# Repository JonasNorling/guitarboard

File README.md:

The Cortex Guitar Board
=======================

This is a Cortex-M4 DSP board for development of audio DSP
applications such as Guitar effects.

This repository contains the hardware design as KiCAD files and sample
software that implements some naive guitar effects. For info about the
software and how to load it, look at [fw/README.md](fw/README.md). For
more on the hardware, keep on reading below and also look in
[hw/README.md](hw/README.md).

The board is based on a STM32F405RG microcontroller (192KiB RAM,
Cortex-M4 with DSP and floating point instructions) and a WM8731 audio
codec.

About the hardware
------------------

### Audio chain

The stereo audio input is pre-amplified in an opamp before the signal
reaches the ADC. This step is required to get a high input impedance
suitable for connecting to an electric guitar or other passive
systems. A WM8731 audio codec is used to digitize the audio signal and
feed it over an I2S bus to the STM32 MCU, and to convert the resulting
signal back into the analog domain. The codec chip includes an
amplifier so the board is capable of driving low-impedance loads such
as headphones.

Note that this isn't quite a HiFi system, though it should be good
enough for casual use. For example, there is some theoretical
crosstalk between the L/R channels on the input side (although you
won't hear it), the codec isn't particularly fancy and expensive, and
the USB power supply isn't very well filtered. If the audio input is
clipping because whatever you're feeding in is too high level (more
than, say, 1V RMS), attenuate it a bit with a resistor divider first.

### Powering the board

The board is designed to be deployed in an effects pedal or box or in
the wiring compartment in an electric guitar. To avoid ground loops it
should run from battery power or an isolated power supply (not mains
earth referenced).

The acceptable input voltage is around 4 to 9 V and the current draw
lands at about 80mA (168MHz, 25% CPU awake) — that should give you
about 24 hours runtime on 4 AA cells.

There is also a micro-USB connector on the board that can be used to
provide power. Note that the USB bus power is connected to the power
input terminal, so avoid connecting another power supply (such as a
battery) at the same time as USB. The USB power from a computer can be
quite noisy, so it may be a bad idea to use it from an audio quality
point of view. Also, connecting the audio output to the same computer
or another grounded system will create funny ground effects that add
additional noise components. Note that there is no inrush current
limit on the USB power line, which is in conflict with requirements in
the USB standard. This might make some USB hosts turn off the port,
although most seem to be just fine with it.

### I/O options

* Micro-USB connector
* 2 LEDs (green and amber, 3mm throughhole) or 2.54mm header
* 2.54mm header with power, 6 analog capable GPIO pins, UART RX/TX and
  1 digital pin
* 3.5mm stereo audio output jack (headphone amplified)
* 3.5mm stereo audio input jack (high impedance)
* optional stereo line-out header
* ARM SWD debug/programming connector, 10-pin 1.27mm pitch

#### MIDI

There are no MIDI ports on board, but the exposed UART pins could be
used to hook up MIDI connectors with a few external parts.

Other resources
---------------

* [Elemental Instruments](http://www.elemental.se)
* [Project on Hackaday.io](https://hackaday.io/project/7936-cortex-guitar-board)

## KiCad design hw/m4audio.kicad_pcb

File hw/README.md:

This directory contains the hardware design in KiCAD format.

Board changelog and errata
--------------------------

### Errata for board revision C

- Line out is missing footprints for some of the resistors recommended
  in the datasheet. It has not been tested.
- Missing a discharge path for the audio input, as recommended in the
  datasheet. I don't think it's necessary in this application.
- There is too much capacitance on the board to comply with the USB
  standard, and inrush current is not limited.
- Silkscreen showing orientation of opamp and codec are unclear on
  finished board.
- Some silkscreen text is too small.
- Drills on TPs are too large for their pads for some processes.
- Solder bridge potential on opamp pins 1 and 2 (doesn't matter).

### Changes in board revision C

- The ground plane has been redesigned; the audio and digital parts
  are now joined in only one point. This was done with the hope of
  minimising audible interference from the MCU.
- Hole and pad sizes for test points have been adjusted, because ITEAD
  Studio had trouble manufacturing rev.B boards without meddling with
  holes and pads.
- Now using two smaller voltage regulators to further separate audio
  and MCU.
- C28, the bulk capacitor before the voltage regulator has been
  removed.
- The diode ORing power from USB or the other connector has been
  removed. It was felt that the voltage drop was slightly troublesome
  and it was better to allow a slightly lower battery voltage instead.
- Footprints for SMD LEDs removed; use 2.54mm header or leaded LEDs.
- Moved stuff around a bit ("optimised component placement").
- RST header.

### Errata for board revision B

- The bulk capacitor upstream of the voltage regulator, C28, should
  not be mounted. It has been discovered that it couples noise from
  the MCU into the ground plane close to the codec. Putting a
  capacitor there makes the audible noise more noticable.
- Putting a resistor (roughly 2-30 ohms) or an inductor in the analog
  power supply path improves audible noise. This can be achieved by
  scraping open the net tie W2 on the backside of the board and
  mounting a 0805 on 1206 resistor there.
- The pin marked PA8 on the silkscreen is in fact not PA8.

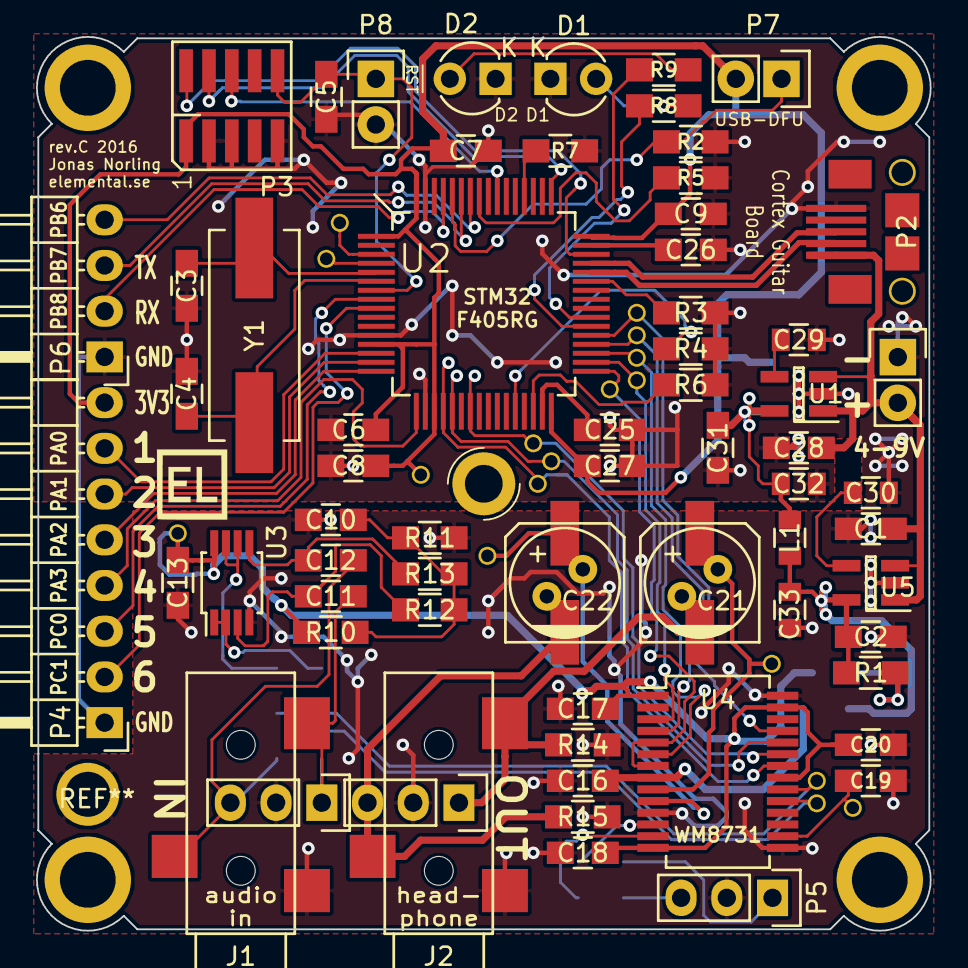
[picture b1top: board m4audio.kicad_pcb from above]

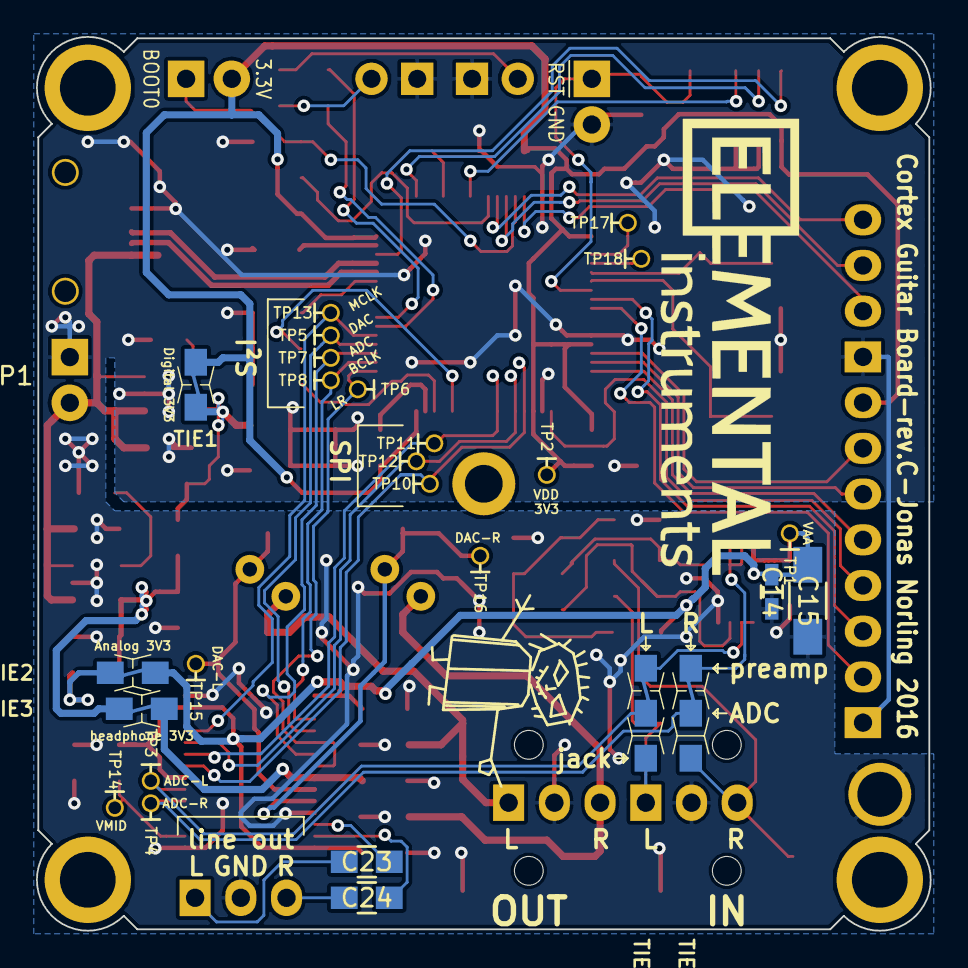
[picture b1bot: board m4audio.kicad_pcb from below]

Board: 2 copper layers, 49.7 x 49.7 mm, 91 parts (26 on the bottom side), 67 nets.

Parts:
C1, C28: 10u16V; C_0805_HandSoldering
C2, C10, C13, C16, C17, C18, C19, C20, C31: 10u; C_0805_HandSoldering
C3, C4: 27p; C_0805_HandSoldering
C5, C7, C8, C9, C11, C12, C27: 100n; C_0805_HandSoldering
C6: 1u; C_0805_HandSoldering
C14: DNP; C_0603_HandSoldering
C15: DNP; C_1206_HandSoldering
C21, C22: 220u; c_elec_6.3x7.7
C23, C24: DNP; C_0805_HandSoldering
C25, C26: 2.2u; C_0805_HandSoldering
C29, C30, C32, C33: DNP; C_0805
D1: green; LED-3MM
D2: orange; LED-3MM
J1, J2: JACK_TRS; 35RASMT2BHNTRX
J11, J21: CONN_01X03; Pin_Header_Straight_1x03
L1: DNP; C_0805
P1, P7, P8: CONN_01X02; Pin_Header_Straight_1x02
P2: USB_OTG; USB_Micro_FCI
P3: CONN_02X05; Pin_Header_SMT_1.27_2x5
P4: CONN_01X08; Pin_Header_Angled_1x08
P5: CONN_01X03; Pin_Header_Straight_1x03
P6: CONN_01X04; Pin_Header_Angled_1x04
R1: 10; R_0805_HandSoldering
R2, R3, R4, R5, R6, R7, R10, R11, R14, R15: 100k; R_0805_HandSoldering
R8, R9: 470; R_0805_HandSoldering
R12, R13: 560k; R_0805_HandSoldering
TIE1: V_D; net_tie_0805
TIE2: V_A; net_tie_0805
TIE3: V_HP; net_tie_0805
TIE4, TIE5: CONN_01X03; net_tie_3_0805
TP1, TP2, TP3, TP4, TP5, TP6, TP7, TP8, TP10, TP11, TP12, TP13, TP14, TP15, TP16, TP17, TP18: TST; TP_0.7mm
U1, U5: AP2210K-3.3; SOT-23-5_Handsoldering
U2: STM32F405RG; QFP50P1200X1200-64
U3: MCP6002; MSOP-8_3x3mm_Pitch0.65mm
U4: WM8731; SSOP-28_5.3x10.2mm_Pitch0.65mm
Y1: 8MHz; Crystal_HC49-SD_SMD

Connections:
/APWR: C2.1, C33.1, L1.1, R1.1, TIE3.2, U5.5
/BOOT0: P7.1, R2.2, U2.60
/BOOT1: R4.2, U2.28
/BYP1: C29.1, U1.4
/BYP2: C30.1, U5.4
/DPWR: C31.1, C32.2, L1.2, TIE1.2, U1.5
/LED1: R8.2, U2.38
/LED2: R9.2, U2.39
/MISC1: P4.7, U2.14
/MISC2: P4.6, U2.15
/MISC3: P4.5, U2.16
/MISC4: P4.4, U2.17
/MISC5: P4.3, U2.8
/MISC6: P4.2, U2.9
/NRST: C5.1, P3.10, P8.1, U2.7
/OSCIN: C3.1, U2.5, Y1.1
/OSCOUT: C4.1, U2.6, Y1.2
/PB6: P6.4, U2.58
/PB7: P6.3, U2.59
/PB8: P6.2, U2.61
/PWR_5V: C1.1, C28.1, P1.2, P2.1, U1.1, U1.3, U5.1, U5.3
/SWCLK: P3.4, U2.49
/SWDIO: P3.2, U2.46
/SWO: P3.6, U2.55
/USB_DM: P2.2, U2.44
/USB_DP: P2.3, U2.45
/VCAP1: C25.1, U2.31
/VCAP2: C26.1, U2.47
/audio/ADCDAT: TP7.1, U2.35, U4.6
/audio/ADCL: TIE4.2, TP3.1, U4.20
/audio/ADCLR: TP6.1, U2.33, U4.5, U4.7
/audio/ADCR: TIE5.2, TP4.1, U4.19
/audio/AIN_L: C11.2, J1.2, J11.1, TIE4.3
/audio/AIN_R: C12.2, J1.3, J11.3, TIE5.3
/audio/AOUT_L: C21.2, J2.2, J21.1, R14.1
/audio/AOUT_R: C22.2, J2.3, J21.3, R15.1
/audio/BCLK: TP8.1, U2.34, U4.3
/audio/CS: TP10.1, U2.20, U4.22
/audio/DACDAT: TP5.1, U2.36, U4.4
/audio/DACL: C21.1, TP15.1, U4.9
/audio/DACR: C22.1, TP16.1, U4.10
/audio/LINEL: C23.1, U4.12
/audio/LINER: C24.1, U4.13
/audio/MCLK: TP13.1, U2.37, U4.25
/audio/MOSI: TP11.1, U2.23, U4.23
/audio/OPINL: C11.1, R12.2, U3.3
/audio/OPINR: C12.1, R13.1, U3.5
/audio/OPOUTL: TIE4.1, U3.1, U3.2
/audio/OPOUTR: TIE5.1, U3.6, U3.7
/audio/SCLK: TP12.1, U2.21, U4.24
/audio/VMID: C19.2, TP14.1, U4.16
/audio/bias: C10.2, R10.1, R11.2, R12.1, R13.2
GND: C1.2, C2.2, C3.2, C4.2, C5.2, C6.2, C7.2, C8.2, C9.2, C10.1, C13.1, C14.1, C15.1, C16.1, C17.1, C18.1, C19.1, C20.1, C25.2, C26.2, C27.2, C28.2, C29.2, C30.2, C31.2, C32.1, C33.2, D1.1, D2.1, J1.1, J2.1, J11.2, J21.2, P1.1, P2.5, P3.3, P3.5, P3.9, P4.1, P5.2, P6.1, P8.2, R2.1, R3.2, R4.1, R5.1, R6.1, R7.1, R11.1, R14.2, R15.2, U1.2, U2.12, U2.18, U2.63, U3.4, U4.11, U4.15, U4.28, U5.2
HPVDD: C16.2, TIE3.1, U4.8
unnamed: C23.2, P5.1
unnamed: C24.2, P5.3
unnamed: D1.2, R8.1
unnamed: D2.2, R9.1
unnamed: R1.2, TIE2.2
unnamed: R3.1, U2.43
unnamed: R5.2, U2.57
unnamed: R6.2, U2.30
unnamed: R7.2, U2.52
unnamed: TP17.1, U2.3
unnamed: TP18.1, U2.4
VAA: C13.2, C14.2, C15.2, C17.2, C18.2, C20.2, R10.2, TIE2.1, TP1.1, U3.8, U4.1, U4.14, U4.21, U4.27
VDD: C6.1, C7.1, C8.1, C9.1, C27.1, P3.1, P4.8, P7.2, TIE1.1, TP2.1, U2.1, U2.13, U2.19, U2.32, U2.48, U2.64

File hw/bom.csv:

Reference,Value,Footprint,Mouser,Notes
C1,10u16V,Capacitors_SMD:C_0805_HandSoldering,81-GRM21BC81C106KE5L,"This Murata is X6S (5.9u biased at 5V)"
C10,10u,Capacitors_SMD:C_0805_HandSoldering,81-GRM21R60J106KE19L,"This Murata is X5R 6.3V (7.5u biased at 3.3V)"
C11,100n,Capacitors_SMD:C_0805_HandSoldering,581-08055C104KAT4A,"This AVX is X7R 50V"
C12,100n,Capacitors_SMD:C_0805_HandSoldering,,
C13,10u,Capacitors_SMD:C_0805_HandSoldering,,
C14,DNP,Capacitors_SMD:C_0603_HandSoldering,,
C15,DNP,Capacitors_SMD:C_1206_HandSoldering,,
C16,10u,Capacitors_SMD:C_0805_HandSoldering,,
C17,10u,Capacitors_SMD:C_0805_HandSoldering,,
C18,10u,Capacitors_SMD:C_0805_HandSoldering,,
C19,10u,Capacitors_SMD:C_0805_HandSoldering,,
C2,10u,Capacitors_SMD:C_0805_HandSoldering,,
C20,10u,Capacitors_SMD:C_0805_HandSoldering,,
C21,220u,Jonas_caps:c_elec_6.3x7.7,647-UUR1C221MCL6GS,
C22,220u,Jonas_caps:c_elec_6.3x7.7,,
C23,DNP,Capacitors_SMD:C_0805_HandSoldering,,
C24,DNP,Capacitors_SMD:C_0805_HandSoldering,,
C25,2.2u,Capacitors_SMD:C_0805_HandSoldering,81-GRM21BR71A225KA01,"This Murata is X7R 10V"
C26,2.2u,Capacitors_SMD:C_0805_HandSoldering,,
C27,100n,Capacitors_SMD:C_0805_HandSoldering,,
C28,10u16V,Capacitors_SMD:C_0805_HandSoldering,,
C29,DNP,Capacitors_SMD:C_0805,,
C3,27p,Capacitors_SMD:C_0805_HandSoldering,80-C0805C270K5G,
C30,DNP,Capacitors_SMD:C_0805,,
C31,10u,Capacitors_SMD:C_0805_HandSoldering,,
C32,DNP,Capacitors_SMD:C_0805,,
C33,DNP,Capacitors_SMD:C_0805,,
C4,27p,Capacitors_SMD:C_0805_HandSoldering,,
C5,100n,Capacitors_SMD:C_0805_HandSoldering,,
C6,1u,Capacitors_SMD:C_0805_HandSoldering,,
C7,100n,Capacitors_SMD:C_0805_HandSoldering,,
C8,100n,Capacitors_SMD:C_0805_HandSoldering,,
C9,100n,Capacitors_SMD:C_0805_HandSoldering,,
D1,green,Footprints:LED-3MM,,
D2,orange,Footprints:LED-3MM,,
J1,JACK_TRS,Jonas_Connectors:35RASMT2BHNTRX,502-35RASMT2BHNTRX,
J11,CONN_01X03,Pin_Headers:Pin_Header_Straight_1x03,,
J2,JACK_TRS,Jonas_Connectors:35RASMT2BHNTRX,,
J21,CONN_01X03,Pin_Headers:Pin_Header_Straight_1x03,,
L1,DNP,Capacitors_SMD:C_0805,,
P1,CONN_01X02,Pin_Headers:Pin_Header_Straight_1x02,,
P2,USB_OTG,Jonas_Connectors:USB_Micro_FCI,649-10118193-0001LF,
P3,CONN_02X05,Jonas_Connectors:Pin_Header_SMT_1.27_2x5,649-202112100010C4LF,
P4,CONN_01X08,Pin_Headers:Pin_Header_Angled_1x08,,
P5,CONN_01X03,Pin_Headers:Pin_Header_Straight_1x03,,
P6,CONN_01X04,Pin_Headers:Pin_Header_Angled_1x04,,
P7,CONN_01X02,Pin_Headers:Pin_Header_Straight_1x02,,
P8,CONN_01X02,Pin_Headers:Pin_Header_Straight_1x02,,
R1,10,Resistors_SMD:R_0805_HandSoldering,,
R10,100k,Resistors_SMD:R_0805_HandSoldering,754-RR1220P-104D,
R11,100k,Resistors_SMD:R_0805_HandSoldering,,
R12,560k,Resistors_SMD:R_0805_HandSoldering,"754-RR1220P-564D ",
R13,560k,Resistors_SMD:R_0805_HandSoldering,,
R14,100k,Resistors_SMD:R_0805_HandSoldering,,
R15,100k,Resistors_SMD:R_0805_HandSoldering,,
R2,100k,Resistors_SMD:R_0805_HandSoldering,,
R3,100k,Resistors_SMD:R_0805_HandSoldering,,
R4,100k,Resistors_SMD:R_0805_HandSoldering,,
R5,100k,Resistors_SMD:R_0805_HandSoldering,,
R6,100k,Resistors_SMD:R_0805_HandSoldering,,
R7,100k,Resistors_SMD:R_0805_HandSoldering,,
R8,470,Resistors_SMD:R_0805_HandSoldering,,
R9,470,Resistors_SMD:R_0805_HandSoldering,,
U1,AP2210K-3.3,Footprints:SOT-23-5_Handsoldering,621-AP2210K-3.3TRG1,"alt: NJM2866F33-TE1, alt: LP2985"
U2,STM32F405RG,Jonas_QFP:QFP50P1200X1200-64,511-STM32F405RGT6,
U3,MCP6002,Housings_SSOP:MSOP-8_3x3mm_Pitch0.65mm,,"MCP6002T-I/MS, LMR358FVM-GTR, TLV272CM8-13"
U4,WM8731,Housings_SSOP:SSOP-28_5.3x10.2mm_Pitch0.65mm,238-WM8731SEDS/V,
U5,AP2210K-3.3,Footprints:SOT-23-5_Handsoldering,,
Y1,Crystal,Crystals:Crystal_HC49-SD_SMD,815-ABLS-8-B2,

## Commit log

2015-08-03 Initial
2015-08-04 PCB updates
2015-08-04 Work...
2015-08-05 Change to electrolytic cap, routing
2015-08-05 Routing...
2015-08-08 Add WM8731 audio codec
2015-08-08 Add a gnome
2015-08-08 Tuning PCB
2015-08-09 Use only one supply net name, add VCAP on STM32, alternative LED footprints
2015-08-09 Tune PCB design, add protection diode
2015-08-09 Add I2S test pads
2015-08-09 Standardise on 100k for random stuff
2015-08-09 Tune values, add BOM
2015-08-09 Adding Gerbers used for OSH Park order
2015-08-11 Basic Eclipse project for the firmware
2015-08-13 Tune build flags and add some code to theoretically make it run
2015-08-13 Eclipse project updates
2015-08-15 Init git submodules in makefile
2015-08-15 Use C11
2015-08-15 WIP: Enable more peripherals
2015-08-15 Build rules for host
2015-08-15 Run in Jack on host
2015-08-29 Board bringup
    - The Codec can output audio though the headphone connectors
2015-08-29 Sinewave example
    There is still plenty of time available per frame.
2015-08-29 DMA data from ADC
2015-08-29 LED abstraction
2015-08-29 Simple delay line example
2015-08-31 Read analog pins
2015-09-06 Start sketching on an fxbox program, misc work
2015-09-06 Add biquad filter core, Wahwah effect, utils for buffer conversion
2015-09-17 Delay effect, the parameterization is still quite weird
2015-09-17 Simple effect selector, idle callback
2015-09-17 Vibrato effect
    knob0 - depth
    knob1 - speed
    knob2 - tubelike distortion
    knob3 - stereo effect (phase difference L/R)
2015-09-22 Effect parameters, scaling
2015-09-24 Recalculate delay each sample, yields smoother changes
2015-09-24 Pitch pedal effect, not very enjoyable
2015-09-26 DFU (USB) programming make rules
2015-09-26 Board update and ripup: split power supply, 49.5mm size
2015-09-26 Remove USB resistor, the STM32 has one built in
2015-09-26 Make TPs a bit larger
2015-09-30 Board...
2015-10-01 Put a 2mm hole in the middle, adjust routing
2015-10-03 Small fixes to routing, silkscreen
2015-10-03 Tidy up routing, add OSHW logo
2015-10-03 Board revision B finished
2015-10-04 Add README file and licenses
2015-10-05 Add missing STM32 library
2015-10-05 Update schematic metadata
2015-10-05 Use Gerber filenames for ITEAD
2015-10-11 Update libopencm3
2015-10-11 Add README.md in the firmware directory
2015-10-25 Add USB connectivity, opening a CDC ACM port for logging
    It's not rock solid, but it seems to enumerate almost every time now.
2015-10-31 Refactor how effects are called
    Using float buffers, move gain/distortion to the common code path.
2015-11-15 Add an experimental "octaver" feedback feature to the delay
    Play back the delay line at double rate and feed it back, creating a
    frequency doubler effect. It sounds interresting, but pretty rough.
2015-11-16 Refactor DSP effects a bit more
2015-11-17 Split up makefiles
    The makefile is divided into platform specific parts.
2015-11-21 Embedded guitar board software
    Support a board embedded in a guitar, with four knobs and a
    three-position switch connected.
    Select the effect to use based on the switch: delay - clean - vibrato.
    - Add functions for setting codec volume
    - Add knob configuration (ADC or GPIO input with pullup)
2016-07-06 Update DFU commands, USB descriptor
2016-07-06 Program for an effects box with switches
2016-07-06 Re-save board with KiCad 4.0, fix small compatibility error
2016-07-06 Turn off reference and value on silkscreen in Gerber
2016-07-08 Adjust testpoint drill and annular, for ITEAD production
2016-07-08 Add RST test point
2016-07-09 Use dual SMT/through hole footprint for caps
2016-07-09 Silkscreen text fixes
2016-07-16 Add delay to fxbox2
2016-07-16 Change LED footprints and resistors, RST header, hole in GND pad
2016-07-24 Redo power supply, split ground plane
    Change to using two SOT-23-5 voltage regulators, one for analog and
    one for digital. Split the ground plane so that digital and analog
    meat at only one point, hoping to improve ground coupled noise
    performance.
    Update silkscreen texts to "rev.C".
    Move silkscreen texts.
2016-07-24 Net tie to bypass the pre-amp
2016-07-25 Tiny silk fixes
2016-07-26 Tiny routing fixes
2016-08-05 Adjust USB interrupts, reset, re-enable USB log
    Logging over USB has been pretty flaky, device enumeration often not
    working. There have been hints that the USB interrupt isn't serviced
    quickly enough, but also about the interrupt not happening at all.
    Trying to fix this by properly setting up interrupt priorities so that
    USB can preempt everything else and get its shit done quickly. Trying
    to reset the USB peripheral more thoroughly, and trying to not block
2016-08-06 Update BOM
2016-08-11 Fix build warnings/errors on older compiler
2016-08-12 Add README about the board layout, update root README
2016-08-12 Add schematic PDF
2016-08-13 Add gerbers for rev.C, move them
2016-08-13 Move value texts, make PDF with assembly drawing
2016-08-13 Convert BOM to CSV format
    So that people without Gnumeric can read it.
2016-08-14 Change LED pins, for rev.C board
    Also make the feedthrough program blink in a more enticing manner.
2016-08-14 Include Kiss FFT
    This is the Kiss FFT library (sourceforge.net/projects/kissfft). After
    testing libfftw3 and getting annoyed at how hard it is to use and
    build and how enormous it is (600KiB!!!), I found Kiss FFT. It is
    slightly faster on Cortex-M3, and very easy to use and build. BSD
    license.
2016-08-14 Noise floor test
2016-08-14 Test crosstalk between channels
2016-08-14 Run THD test on both channels simultaneously
2016-08-14 Measure THD using FFT
2016-08-14 Run multiple THD tests
2016-08-14 Use a precomputed window for the FFT
2016-08-21 Remove a leftover sqrt that broke THD numbers
2016-08-21 Update BOM/schematic with component choices
    Using MCP6002 opamp, 10 ohms impedance on analog supply, not
    populating voltage regulator bypass cap by default.
2016-08-24 Read the right audio-in DMA buffer at the right time
    It seems like we've been reading the wrong buffer, but getting away
    with it because we generally read the samples right away to convert
    them to floats.
    Now using the "input" DMA interrupt, which comes 20us later, because
    the last sample hasn't been DMA's in yet when the "output" interrupt
    comes.
2016-08-24 Disable automatic high-pass in ADC, doing it in software
    This fixes some noise issues with the WM8731 codec, for some weird
    reasons. The ADC really doesn't like it when it's quiet, when it's
    sitting just around digital 0, and it seems to start to invent
    noise. Disabling removing of the DC bias (an offset which seems to be
    internal to the codec anyway) makes the signal much cleaner when the
    input is absolutely quiet. The DC bias is now removed in software
2016-08-24 USB audio, forwarding incomming sound over USB
    There is no synchronisation implemented, which makes the sound go
    funny sometimes.
    Some workarounds for missing functionality in libopencm3, using code
    snippets from open pull requests on GitHub and other projects I found.
2016-09-03 USB audio: send the right number of samples each frame
    We run in asynchronous mode and send the number of samples that are
    actually available per USB frame to the host. How many samples have
    trickled in since the last USB frame is deduced by looking at where
    the DMA job writes to the input buffer when it's time to fill the USB
    buffer.
    I think there may be artefacts when starting to send audio; the code
2016-09-24 Fixes for fxbox (wahwah pedal program)
2016-09-24 Make WM8731 highpass build-time configurable
    With the automatic DC removal disabled the ADC range is narrower,
    leading to more clipping in some situations. It is now disabled by
    default, but can be enabled by uncommenting a line in wm8731.c.
    Also, change FFT test parameters.
2018-03-19 Time how long it takes to process each frame
2018-03-23 Embryo saw wavewatble synth
2018-03-23 Enable caches and prefetch
2018-03-23 Improve wavetable synth
2018-03-24 Sawsynth: add lowpass filter
2018-03-28 Sawsynth: volume and filter envelopes
2019-08-03 Create LICENSE
2021-07-10 Test actions
